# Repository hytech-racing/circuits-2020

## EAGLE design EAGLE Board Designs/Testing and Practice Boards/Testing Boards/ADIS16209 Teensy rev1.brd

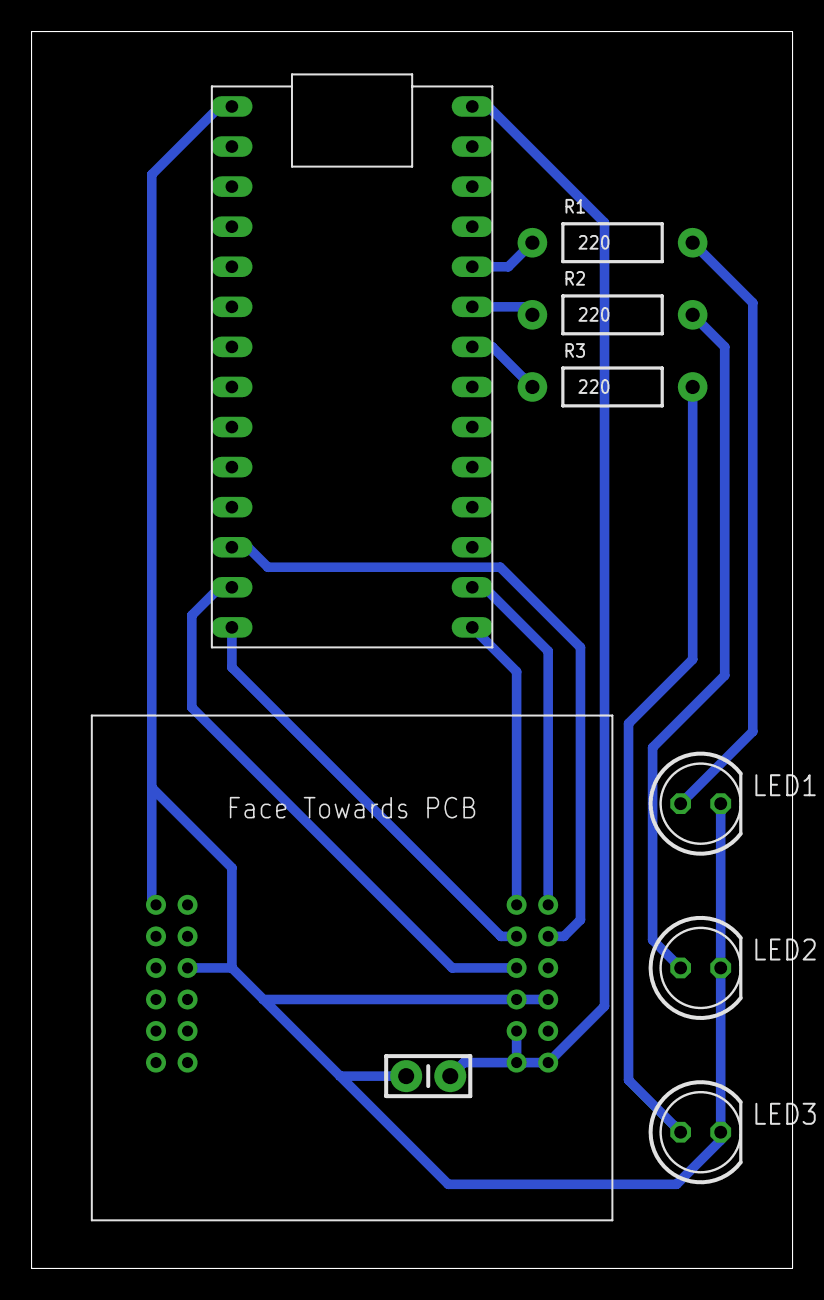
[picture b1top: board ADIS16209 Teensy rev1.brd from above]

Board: 2 copper layers, 48.2 x 78.4 mm, 9 parts (0 on the bottom side), 13 nets.

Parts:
C1: 1uF; CAP-PTH-SMALL-KIT
LED1, LED2, LED3: LED-5MM
R1, R2, R3: 220; AXIAL-0.4
U$1: ADIS16209/PCB
U$2: TEENSY_3.2_SIMPLE

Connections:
+3V3: C1.2, U$1.P$10, U$1.P$11, U$1.P$12, U$2.VIN
CS: U$1.P$3, U$2.D10(TX2)
GND: C1.1, LED1.K, LED2.K, LED3.K, U$1.P$7, U$1.P$8, U$1.P$14, U$1.P$17, U$2.GND
MISO: U$1.P$4, U$2.D12
MOSI: U$1.P$6, U$2.D11
unnamed: LED1.A, R1.P$2
unnamed: U$1.P$1, U$2.A0
unnamed: R1.P$1, U$2.A8
unnamed: R2.P$1, U$2.A7
unnamed: R3.P$1, U$2.A6
unnamed: LED2.A, R2.P$2
unnamed: LED3.A, R3.P$2
SCK: U$1.P$2, U$2.D13

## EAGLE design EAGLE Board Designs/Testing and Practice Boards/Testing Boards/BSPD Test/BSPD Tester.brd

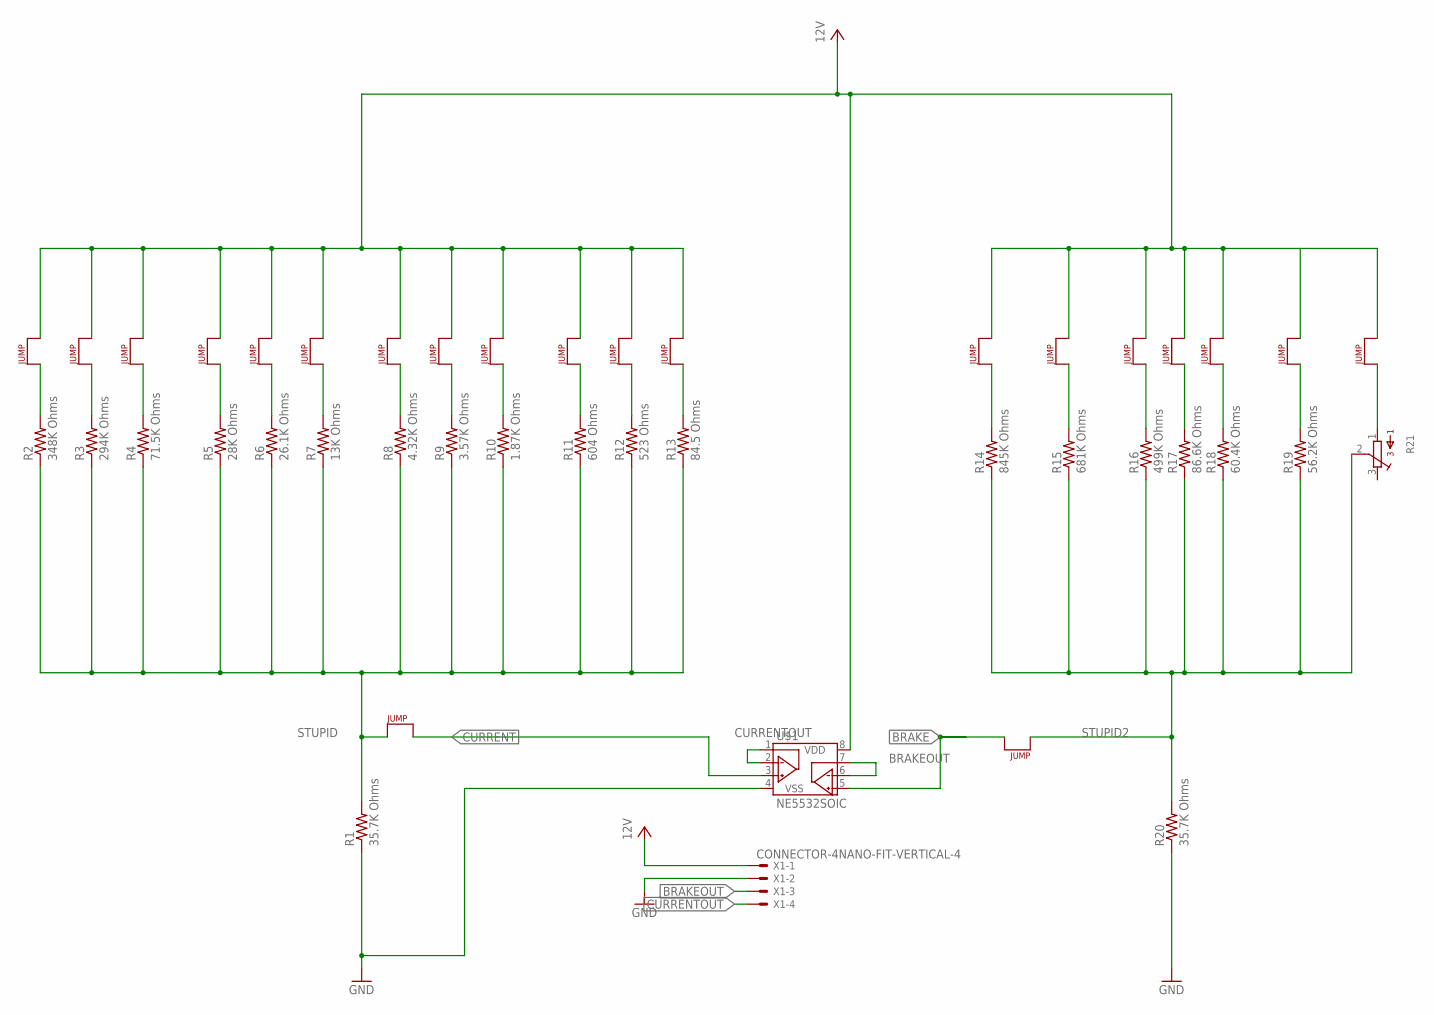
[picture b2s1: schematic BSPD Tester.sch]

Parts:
J1, J2, J3, J4, J5, J6, J7, J8, J9, J10, J11, J12, J13, J14, J15, J16, J17, J18, J19, J20, J21: JUMPER.1; 1X02
R1, R20: 35.7K Ohms; 1206
R2: 348K Ohms; 1206
R3: 294K Ohms; 1206
R4: 71.5K Ohms; 1206
R5: 28K Ohms; 1206
R6: 26.1K Ohms; 1206
R7: 13K Ohms; 1206
R8: 4.32K Ohms; 1206
R9: 3.57K Ohms; 1206
R10: 1.87K Ohms; 1206
R11: 604 Ohms; 1206
R12: 523 Ohms; 1206
R13: 84.5 Ohms; 1206
R14: 845K Ohms; 1206
R15: 681K Ohms; 1206
R16: 499K Ohms; 1206
R17: 86.6K Ohms; 1206
R18: 60.4K Ohms; 1206
R19: 56.2K Ohms; 1206
R21: TRIMPOT_3296C; TRIMPOT_3296
U$1: NE5532SOIC; SOIC-08
X1: CONNECTOR-4NANO-FIT-VERTICAL-4; NANO-FIT_VERTICAL-4

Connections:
BRAKE: J21.2, U$1.5 (VINB+)
BRAKEOUT: U$1.6 (VINB-), U$1.7 (VOUTB), X1.P$3
CURRENT: J19.2, U$1.3 (VINA+)
CURRENTOUT: U$1.1 (VOUTA), U$1.2 (VINA-), X1.P$4
GND: R1.1, R20.1, U$1.4 (VSS), X1.P$2
unnamed: J1.1, R2.2
unnamed: J13.1, R14.2
unnamed: J2.1, R3.2
unnamed: J3.1, R4.2
unnamed: J4.1, R5.2
unnamed: J5.1, R6.2
unnamed: J6.1, R7.2
unnamed: J7.1, R8.2
unnamed: J8.1, R9.2
unnamed: J9.1, R10.2
unnamed: J10.1, R11.2
unnamed: J11.1, R12.2
unnamed: J12.1, R13.2
unnamed: J14.1, R15.2
unnamed: J15.1, R16.2
unnamed: J16.1, R17.2
unnamed: J17.1, R18.2
unnamed: J18.1, R19.2
unnamed: J20.1, R21.1
STUPID: J19.1, R1.2, R2.1, R3.1, R4.1, R5.1, R6.1, R7.1, R8.1, R9.1, R10.1, R11.1, R12.1, R13.1
STUPID2: J21.1, R14.1, R15.1, R16.1, R17.1, R18.1, R19.1, R20.2, R21.2
VCC: J1.2, J2.2, J3.2, J4.2, J5.2, J6.2, J7.2, J8.2, J9.2, J10.2, J11.2, J12.2, J13.2, J14.2, J15.2, J16.2, J17.2, J18.2, J20.2, U$1.8 (VDD), X1.P$1

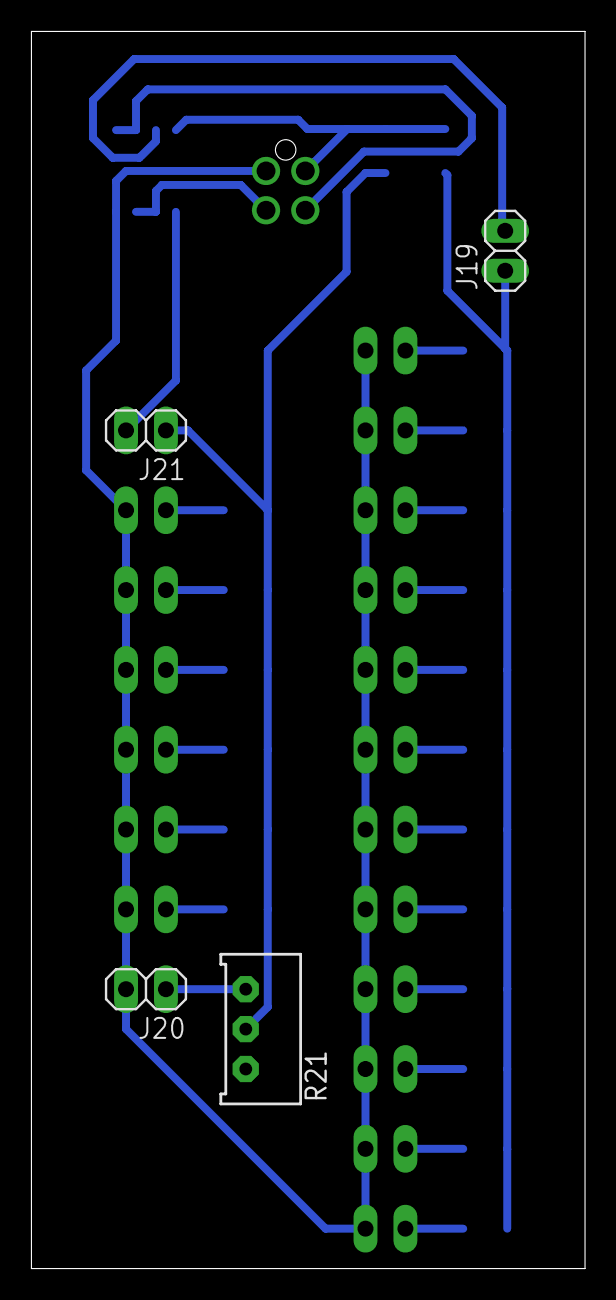
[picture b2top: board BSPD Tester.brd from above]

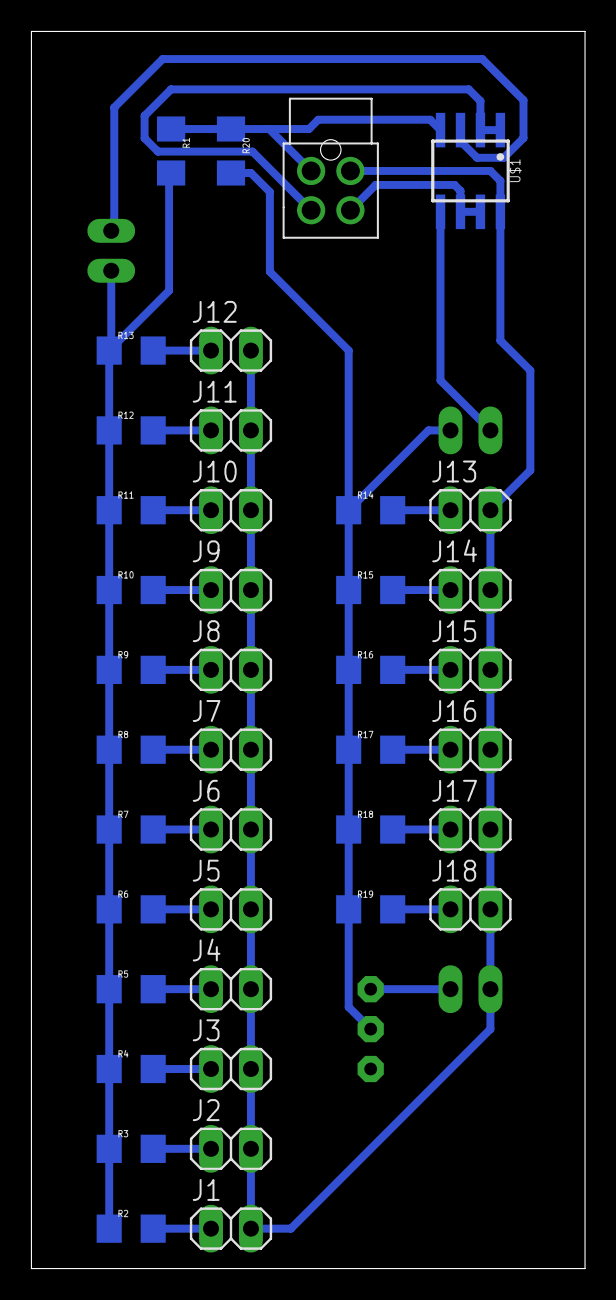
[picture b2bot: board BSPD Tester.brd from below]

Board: 2 copper layers, 35.2 x 78.7 mm, 44 parts (40 on the bottom side), 27 nets.

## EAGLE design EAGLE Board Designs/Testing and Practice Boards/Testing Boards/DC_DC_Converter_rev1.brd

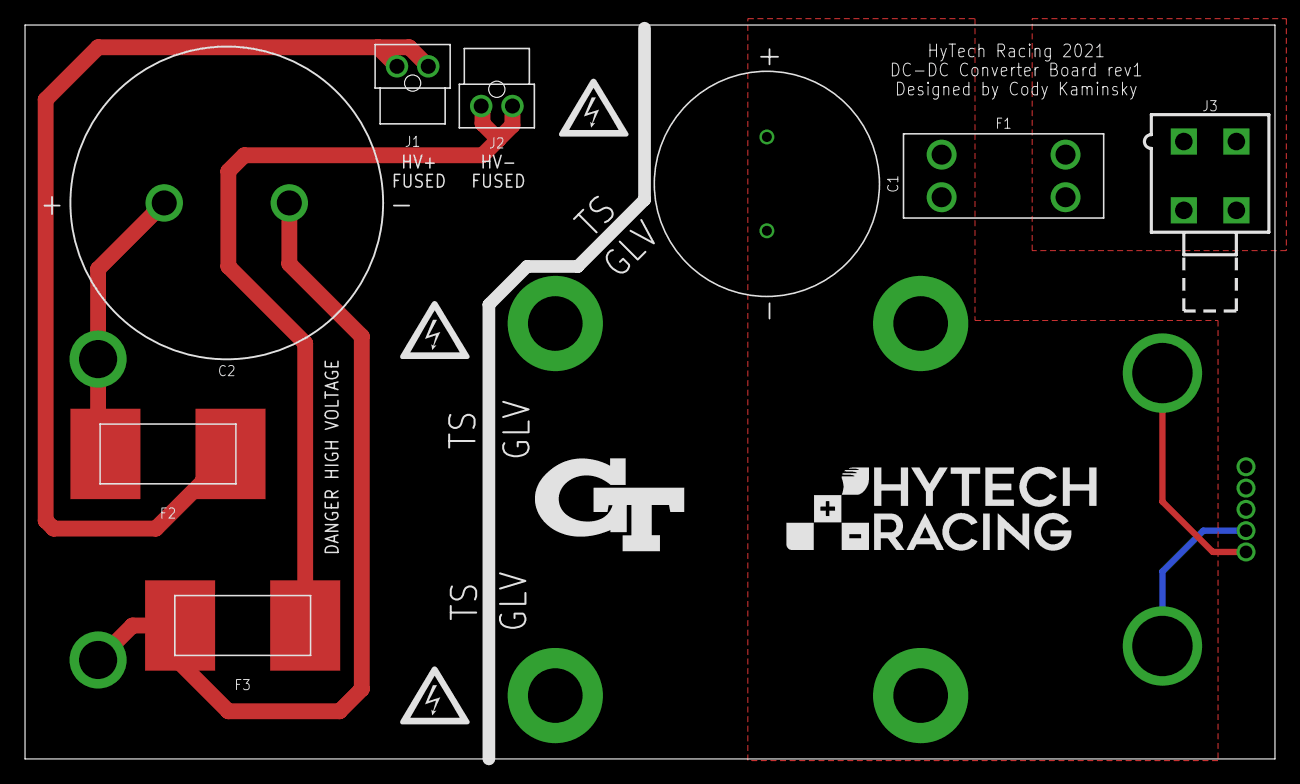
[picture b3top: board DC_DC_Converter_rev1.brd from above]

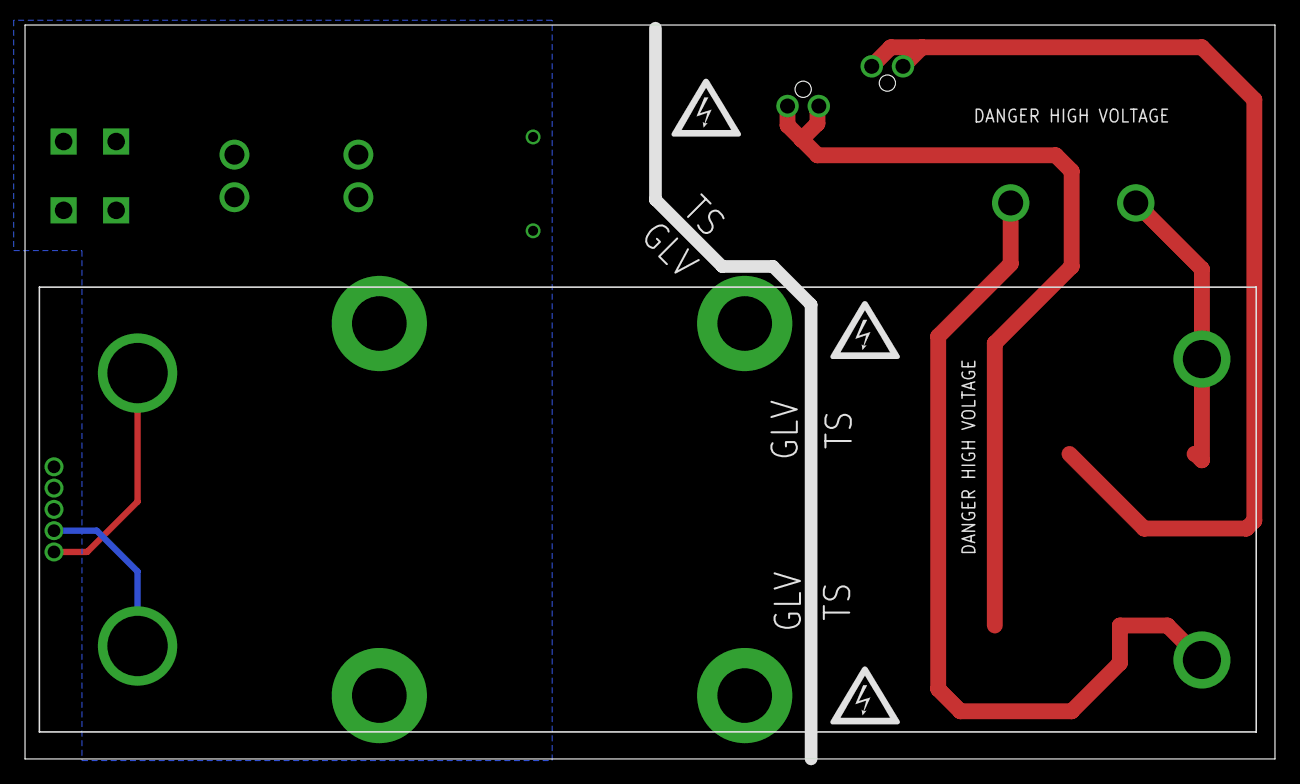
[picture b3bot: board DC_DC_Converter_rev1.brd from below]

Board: 2 copper layers, 99.9 x 58.7 mm, 17 parts (4 on the bottom side), 7 nets.

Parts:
C1: 4.7 mF; EKYC*MM
C2: LGG2G181MELA25; L*A
F1: MINI-BLADE_FUSE_HOLDER
F2, F3: 885_FUSE; 0885
J1, J2: MOLEX_NANOFIT_PTH_02
J3: MOLEX_MINIFIT_PTH_04
U1: DCM3714BD2K13E0C09; 3714DCM_VIA
U$1, U$2, U$3, U$8, U$9, U$10: HV_0.50"
U$6: LOGO_HYTECH_1.0"
U$7: LOGO_GT_0.50"

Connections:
12V_UNFUSED: C1.+, F1.L1, F1.L2, U1.3, U1.9
+12V: F1.R1, F1.R2, J3.1, J3.2
GND: C1.-, J3.3, J3.4, U1.4, U1.8
HV+: F2.1, J1.1, J1.2
HV-: F3.1, J2.1, J2.2
IN+: C2.+, F2.2, U1.1
IN-: C2.-, F3.2, U1.2

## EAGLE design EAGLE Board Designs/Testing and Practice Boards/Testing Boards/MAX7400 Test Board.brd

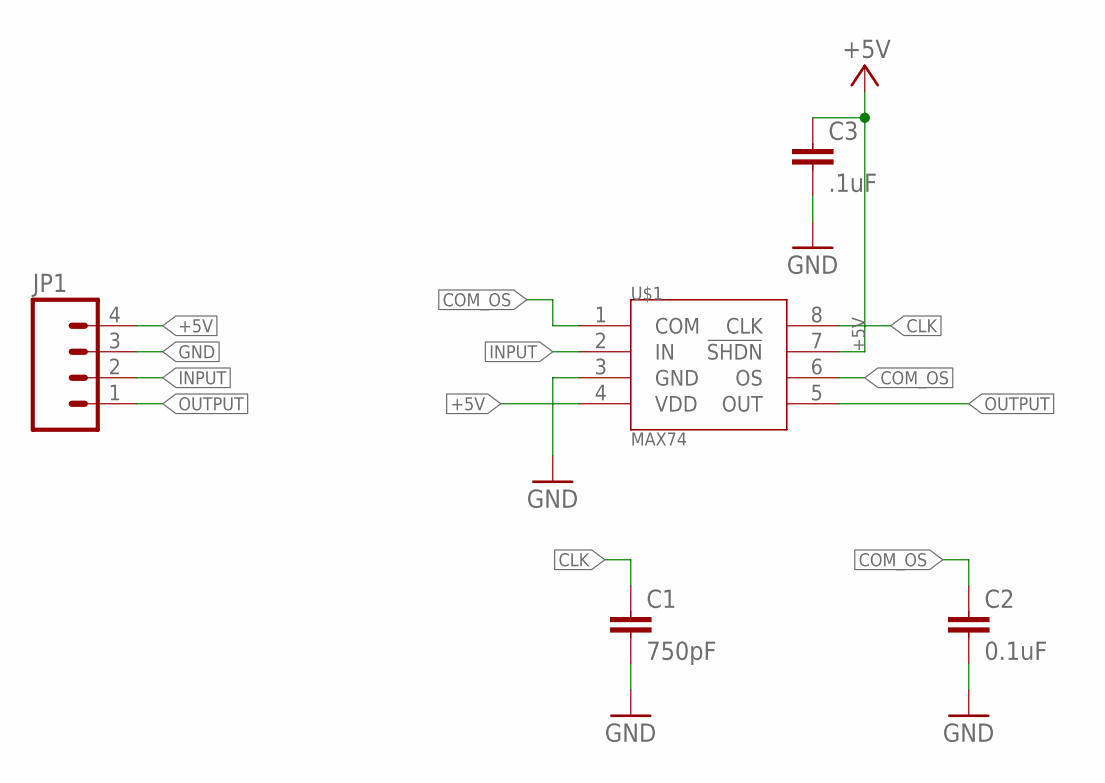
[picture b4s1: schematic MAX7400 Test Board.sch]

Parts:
C1: 750pF; 0603-CAP
C2: 0.1uF; 0603-CAP
C3: .1uF; 0603-CAP
JP1: M04; 1X04
U$1: MAX74; SOP8

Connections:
+5V: C3.1, JP1.4, U$1.4 (VDD), U$1.7 (!SHDN)
CLK: C1.1, U$1.8 (CLK)
COM_OS: C2.1, U$1.1 (COM), U$1.6 (OS)
GND: C1.2, C2.2, C3.2, JP1.3, U$1.3 (GND)
INPUT: JP1.2, U$1.2 (IN)
OUTPUT: JP1.1, U$1.5 (OUT)

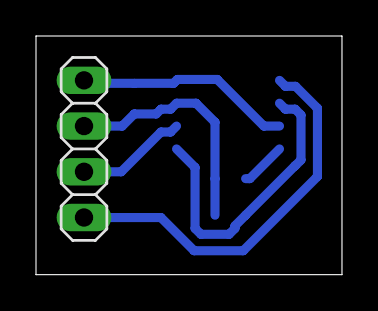
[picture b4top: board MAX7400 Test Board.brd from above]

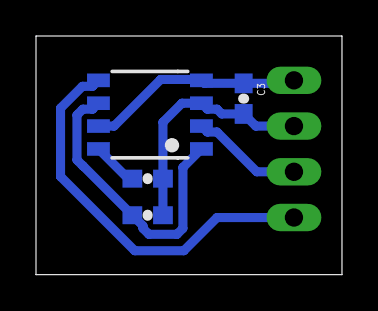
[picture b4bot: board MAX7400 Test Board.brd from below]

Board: 2 copper layers, 17.0 x 13.3 mm, 5 parts (4 on the bottom side), 6 nets.

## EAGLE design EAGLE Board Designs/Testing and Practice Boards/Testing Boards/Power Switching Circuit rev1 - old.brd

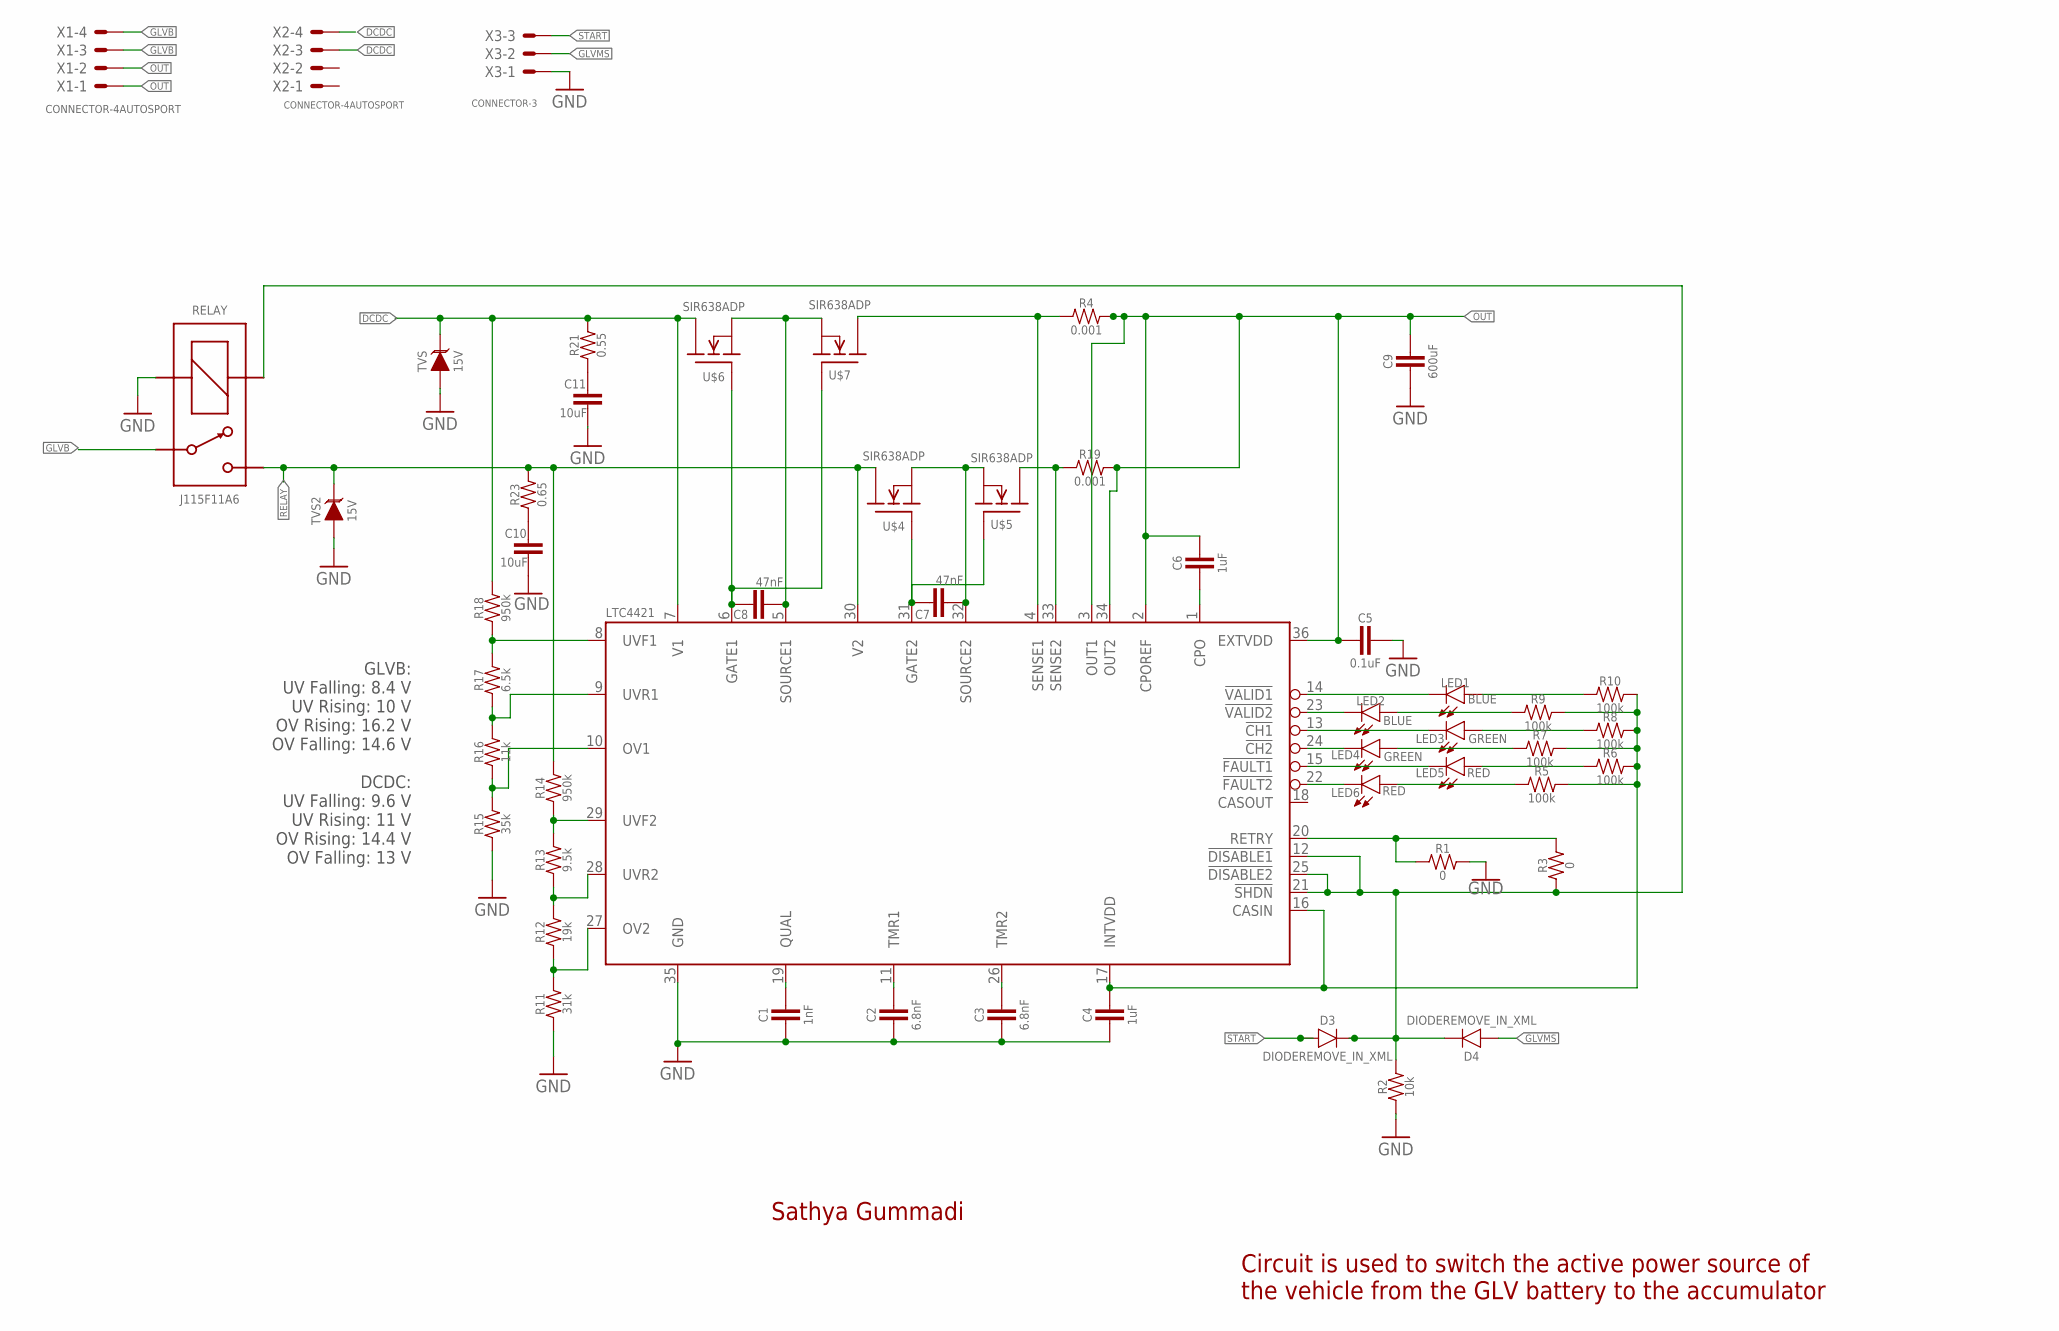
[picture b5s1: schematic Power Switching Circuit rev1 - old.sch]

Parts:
C1: 1nF; 0603-CAP
C2, C3: 6.8nF; 0603-CAP
C4, C6: 1uF; 0603-CAP
C5: 0.1uF; 0603-CAP
C7, C8: 47nF; 0603-CAP
C9: 600uF; 0603-CAP
C10, C11: 10uF; 0603-CAP
D3, D4: DIODEREMOVE_IN_XML; 0805_D
LED1, LED2: BLUE; LED-603
LED3, LED4: GREEN; LED-603
LED5, LED6: RED; LED-603
LTC4421: LTC4421; SSOP-36
R1, R3: 0; 0603-RES
R2: 10k; 0603-RES
R4, R19: 0.001; 5930-SENSE_RES
R5, R6, R7, R8, R9, R10: 100k; 0603-RES
R11: 31k; 0603-RES
R12: 19k; 0603-RES
R13: 9.5k; 0603-RES
R14, R18: 950k; 0603-RES
R15: 35k; 0603-RES
R16: 11k; 0603-RES
R17: 6.5k; 0603-RES
R21: 0.55; 0805
R23: 0.65; 0805
RELAY: J115F11A6; J115F11A*6*
TVS, TVS2: TVS_15V; SOT-23
U$4, U$5, U$6, U$7: SIR638ADP; SO-8-POWERPAK
X1, X2: CONNECTOR-4AUTOSPORT; AUTOSPORT_12-04
X3: CONNECTOR-3; AUTOSPORT_04-35

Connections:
!CH1: LED3.C, LTC4421.13 (!CH1)
!CH2: LED4.C, LTC4421.24 (!CH2)
!FAULT1: LED5.C, LTC4421.15 (!FAULT1)
!FAULT2: LED6.C, LTC4421.22 (!FAULT2)
!SHDN: D3.C, D4.C, LTC4421.12 (!DISABLE1), LTC4421.21 (!SHDN), LTC4421.25 (!DISABLE2), R2.2, R3.1, RELAY.COIL1 (COIL+)
!VALID1: LED1.C, LTC4421.14 (!VALID1)
!VALID2: LED2.C, LTC4421.23 (!VALID2)
CASIN: C4.1, LTC4421.16 (CASIN), LTC4421.17 (INTVDD), R5.2, R6.2, R7.2, R8.2, R9.2, R10.2
CPO: C6.2, LTC4421.1 (CPO)
DCDC: LTC4421.7 (V1), R18.2, R21.2, TVS.3 (C), U$6.D@5 (D), U$6.D@6 (D), U$6.D@7 (D), U$6.D@8 (D), U$6.D@PAD (D), X2.3, X2.4
GATE1: C8.2, LTC4421.6 (GATE1), U$6.4 (G), U$7.4 (G)
GATE2: C7.2, LTC4421.31 (GATE2), U$4.4 (G), U$5.4 (G)
GLVB: RELAY.CONTACT1, X1.3, X1.4
GLVMS: D4.A, X3.B
GND: C1.2, C2.2, C3.2, C4.2, C5.1, C9.2, C10.2, C11.2, LTC4421.35 (GND), R1.2, R2.1, R11.1, R15.1, RELAY.COIL2 (COIL-), TVS.1 (A), TVS2.1 (A), X3.A
unnamed: C1.1, LTC4421.19 (QUAL)
unnamed: C2.1, LTC4421.11 (TMR1)
unnamed: C3.1, LTC4421.26 (TMR2)
unnamed: C10.1, R23.1
unnamed: LED6.A, R5.1
unnamed: LED5.A, R6.1
unnamed: LED4.A, R7.1
unnamed: LED3.A, R8.1
unnamed: LED2.A, R9.1
unnamed: LED1.A, R10.1
unnamed: C11.1, R21.1
OUT: C5.2, C6.1, C9.1, LTC4421.2 (CPOREF), LTC4421.3 (OUT1), LTC4421.34 (OUT2), LTC4421.36 (EXTVDD), R4.2, R19.2, X1.1, X1.2
OV1: LTC4421.10 (OV1), R15.2, R16.1
OV2: LTC4421.27 (OV2), R11.2, R12.1
RELAY: LTC4421.30 (V2), R14.2, R23.2, RELAY.CONTACT2 (S), TVS2.3 (C), U$4.D@5 (D), U$4.D@6 (D), U$4.D@7 (D), U$4.D@8 (D), U$4.D@PAD (D)
RETRY: LTC4421.20 (RETRY), R1.1, R3.2
SENSE: LTC4421.4 (SENSE1), R4.1, U$7.D@5 (D), U$7.D@6 (D), U$7.D@7 (D), U$7.D@8 (D), U$7.D@PAD (D)
SENSE2: LTC4421.33 (SENSE2), R19.1, U$5.D@5 (D), U$5.D@6 (D), U$5.D@7 (D), U$5.D@8 (D), U$5.D@PAD (D)
SOURCE1: C8.1, LTC4421.5 (SOURCE1), U$6.1 (S), U$6.2 (S), U$6.3 (S), U$7.1 (S), U$7.2 (S), U$7.3 (S)
SOURCE2: C7.1, LTC4421.32 (SOURCE2), U$4.1 (S), U$4.2 (S), U$4.3 (S), U$5.1 (S), U$5.2 (S), U$5.3 (S)
START: D3.A, X3.C
UVF1: LTC4421.8 (UVF1), R17.2, R18.1
UVF2: LTC4421.29 (UVF2), R13.2, R14.1
UVR1: LTC4421.9 (UVR1), R16.2, R17.1
UVR2: LTC4421.28 (UVR2), R12.2, R13.1

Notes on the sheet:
Sathya Gummadi
Circuit is used to switch the active power source of the vehicle from the GLV battery to the accumulator
GLVB: UV Falling: 8.4 V UV Rising: 10 V OV Rising: 16.2 V OV Falling: 14.6 V DCDC: UV Falling: 9.6 V UV Rising: 11 V OV Rising: 14.4 V OV Falling: 13 V

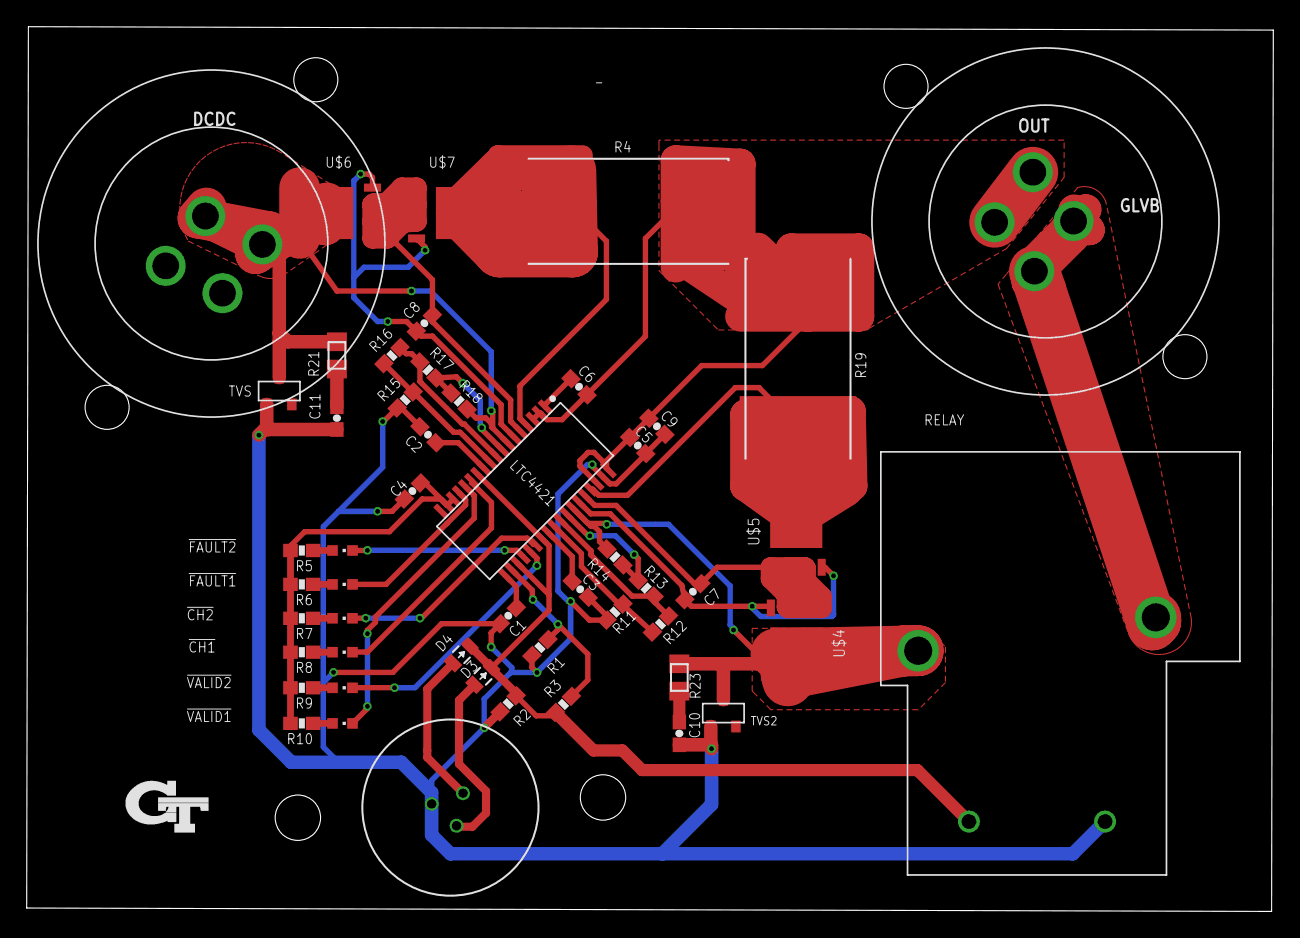
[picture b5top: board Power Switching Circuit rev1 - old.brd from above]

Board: 2 copper layers, 93.4 x 66.3 mm, 51 parts (0 on the bottom side), 40 nets.

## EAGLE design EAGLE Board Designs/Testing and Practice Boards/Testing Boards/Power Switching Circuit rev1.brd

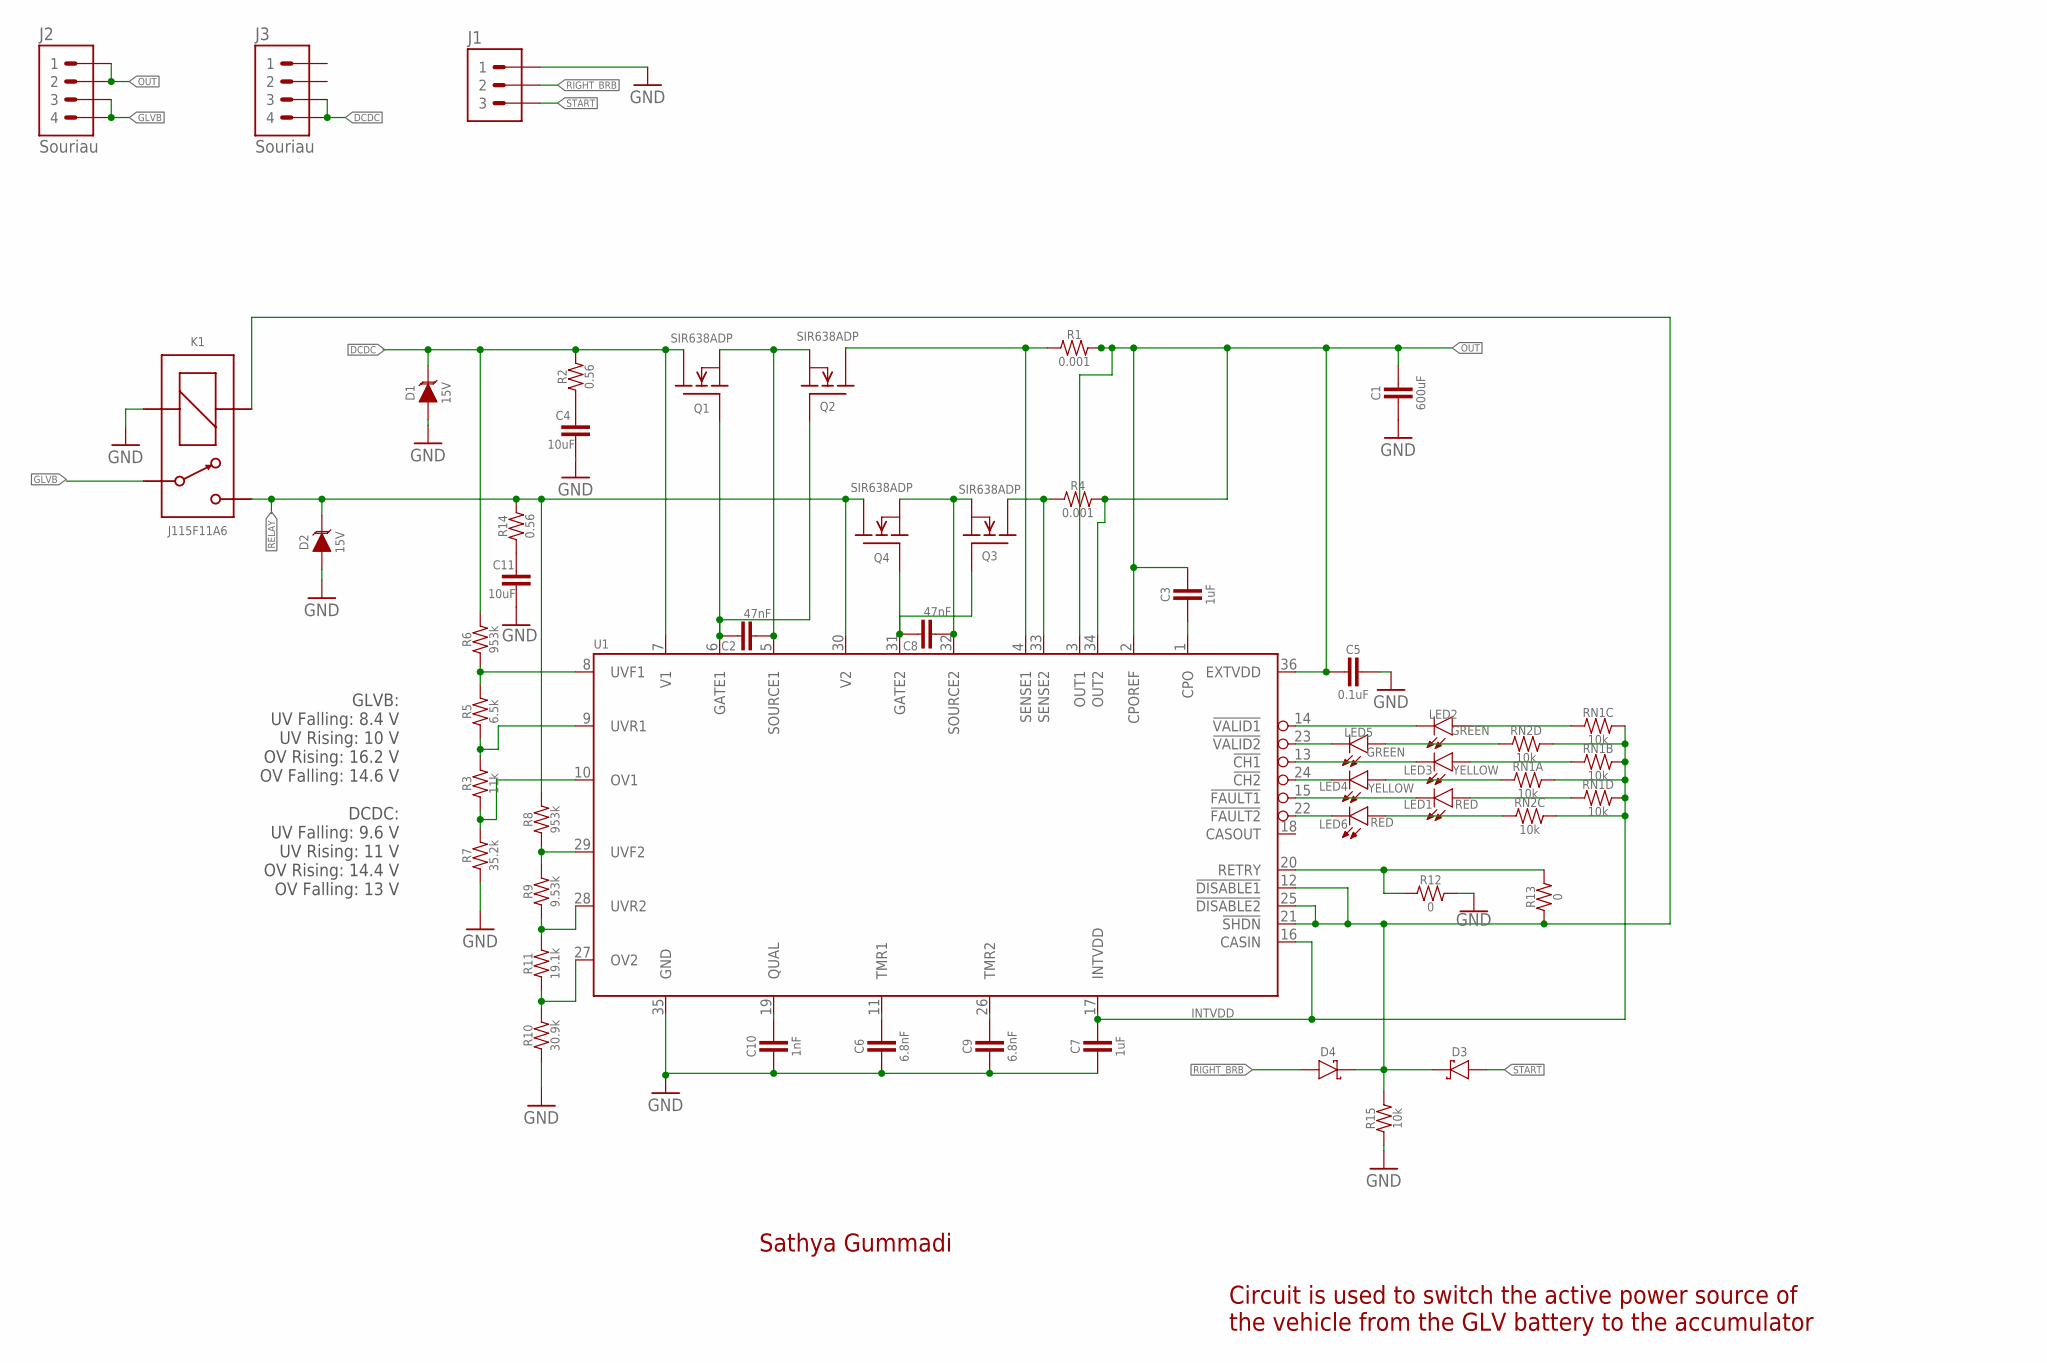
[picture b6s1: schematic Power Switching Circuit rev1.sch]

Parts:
C1: 600uF; 0603-CAP
C2, C8: 47nF; 0603-CAP
C3, C7: 1uF; 0603-CAP
C4, C11: 10uF; 0603-CAP
C5: 0.1uF; 0603-CAP
C6, C9: 6.8nF; 0603-CAP
C10: 1nF; 0603-CAP
D1, D2: TVS_15V; SOT-23
D3, D4: SCHOTTKY; CLP1608-2L
J1: CONNECTOR-3_; SOURIAU_04-35
J2, J3: CONNECTOR-4_SOURIAU_; SOURIAU_12-04
K1: J115F11A6; J115F11A*6*
LED1, LED6: RED; LED-603
LED2, LED5: GREEN; LED-603
LED3, LED4: YELLOW; LED-603
Q1, Q2, Q3, Q4: SIR638ADP; POWERPAK_SO-8
R1, R4: 0.001; 5930-SENSE_RES
R2, R14: 0.56; 0805
R3: 11k; 0603-RES
R5: 6.5k; 0603-RES
R6, R8: 953k; 0603-RES
R7: 35.2k; 0603-RES
R9: 9.53k; 0603-RES
R10: 30.9k; 0603-RES
R11: 19.1k; 0603-RES
R12, R13: 0; 0603-RES
R15: 10k; 0603-RES
RN1, RN2: RESISTOR_NETWORK_4_10K; YC/TC164
U1: LTC4421; SSOP-36

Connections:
!CH1: LED3.C, U1.13 (!CH1)
!CH2: LED4.C, U1.24 (!CH2)
!FAULT1: LED1.C, U1.15 (!FAULT1)
!FAULT2: LED6.C, U1.22 (!FAULT2)
!SHDN!: D3.2 (C), D4.2 (C), K1.COIL1 (COIL+), R13.1, R15.2, U1.12 (!DISABLE1), U1.21 (!SHDN), U1.25 (!DISABLE2)
!VALID1: LED2.C, U1.14 (!VALID1)
!VALID2: LED5.C, U1.23 (!VALID2)
CPO: C3.2, U1.1 (CPO)
DCDC: D1.3 (C), J3.3, J3.4, Q1.D@5 (D), Q1.D@6 (D), Q1.D@7 (D), Q1.D@8 (D), Q1.D@PAD (D), R2.2, R6.2, U1.7 (V1)
GATE1: C2.2, Q1.4 (G), Q2.4 (G), U1.6 (GATE1)
GATE2: C8.2, Q3.4 (G), Q4.4 (G), U1.31 (GATE2)
GLVB: J2.3, J2.4, K1.CONTACT1
GND: C1.2, C4.2, C5.1, C6.2, C7.2, C9.2, C10.2, C11.2, D1.1 (A), D2.1 (A), J1.A (1), K1.COIL2 (COIL-), R7.1, R10.1, R12.2, R15.1, U1.35 (GND)
INTVDD: C7.1, RN1.5 (2), RN1.6 (2), RN1.7 (2), RN1.8 (2), RN2.5 (2), RN2.6 (2), U1.16 (CASIN), U1.17 (INTVDD)
unnamed: C10.1, U1.19 (QUAL)
unnamed: C6.1, U1.11 (TMR1)
unnamed: C9.1, U1.26 (TMR2)
unnamed: C11.1, R14.1
unnamed: LED6.A, RN2.3 (1)
unnamed: LED1.A, RN1.4 (1)
unnamed: LED4.A, RN1.1
unnamed: LED3.A, RN1.2 (1)
unnamed: LED5.A, RN2.4 (1)
unnamed: LED2.A, RN1.3 (1)
unnamed: C4.1, R2.1
OUT: C1.1, C3.1, C5.2, J2.1, J2.2, R1.2, R4.2, U1.2 (CPOREF), U1.3 (OUT1), U1.34 (OUT2), U1.36 (EXTVDD)
OV1: R3.1, R7.2, U1.10 (OV1)
OV2: R10.2, R11.1, U1.27 (OV2)
RELAY: D2.3 (C), K1.CONTACT2 (S), Q4.D@5 (D), Q4.D@6 (D), Q4.D@7 (D), Q4.D@8 (D), Q4.D@PAD (D), R8.2, R14.2, U1.30 (V2)
RETRY: R12.1, R13.2, U1.20 (RETRY)
RIGHT_BRB: D4.1 (A), J1.B (2)
SENSE: Q2.D@5 (D), Q2.D@6 (D), Q2.D@7 (D), Q2.D@8 (D), Q2.D@PAD (D), R1.1, U1.4 (SENSE1)
SENSE2: Q3.D@5 (D), Q3.D@6 (D), Q3.D@7 (D), Q3.D@8 (D), Q3.D@PAD (D), R4.1, U1.33 (SENSE2)
SOURCE1: C2.1, Q1.1 (S), Q1.2 (S), Q1.3 (S), Q2.1 (S), Q2.2 (S), Q2.3 (S), U1.5 (SOURCE1)
SOURCE2: C8.1, Q3.1 (S), Q3.2 (S), Q3.3 (S), Q4.1 (S), Q4.2 (S), Q4.3 (S), U1.32 (SOURCE2)
START: D3.1 (A), J1.C (3)
UVF1: R5.2, R6.1, U1.8 (UVF1)
UVF2: R8.1, R9.2, U1.29 (UVF2)
UVR1: R3.2, R5.1, U1.9 (UVR1)
UVR2: R9.1, R11.2, U1.28 (UVR2)

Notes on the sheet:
Sathya Gummadi
Circuit is used to switch the active power source of the vehicle from the GLV battery to the accumulator
GLVB: UV Falling: 8.4 V UV Rising: 10 V OV Rising: 16.2 V OV Falling: 14.6 V DCDC: UV Falling: 9.6 V UV Rising: 11 V OV Rising: 14.4 V OV Falling: 13 V

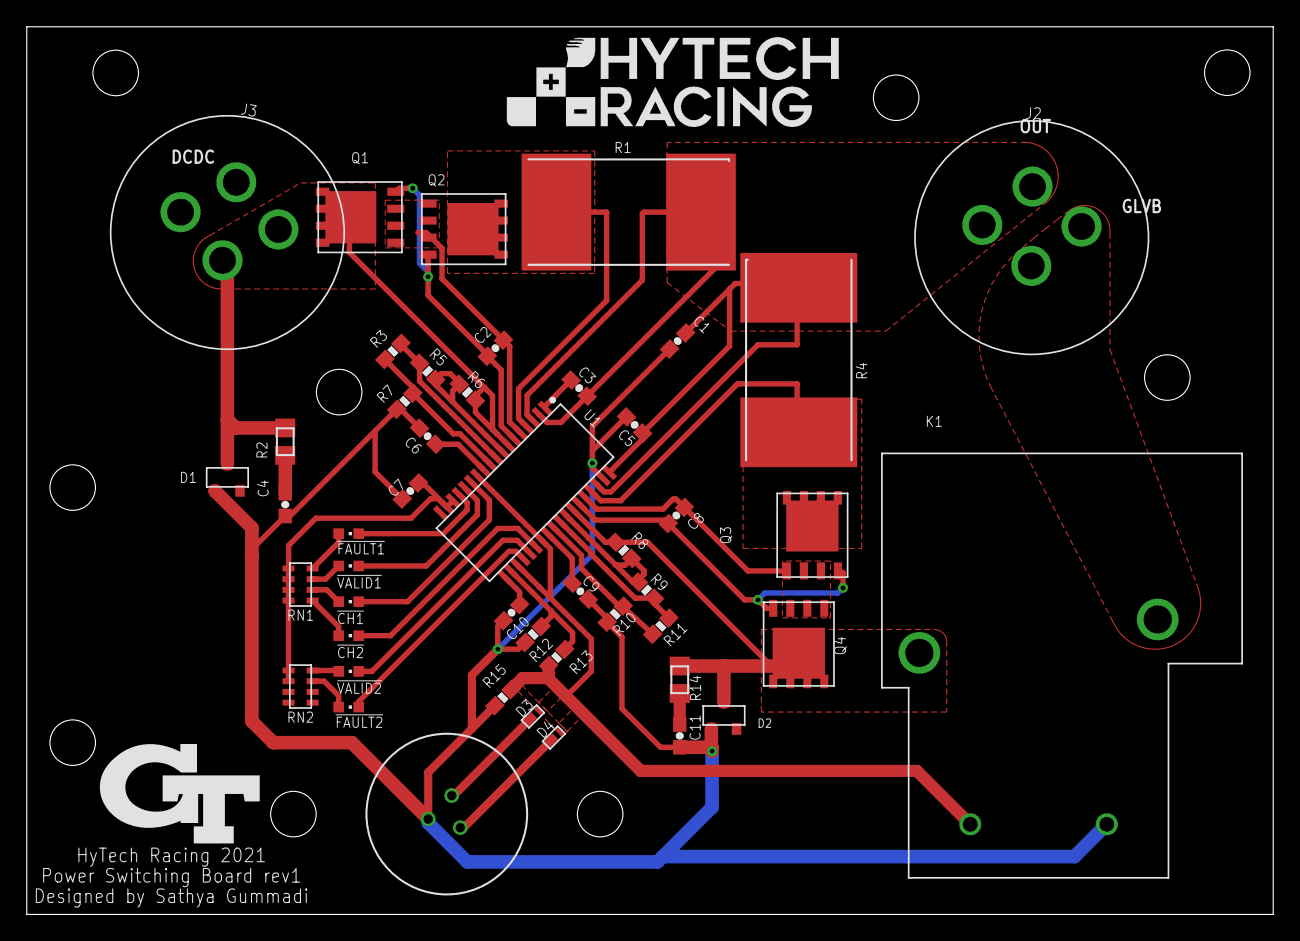
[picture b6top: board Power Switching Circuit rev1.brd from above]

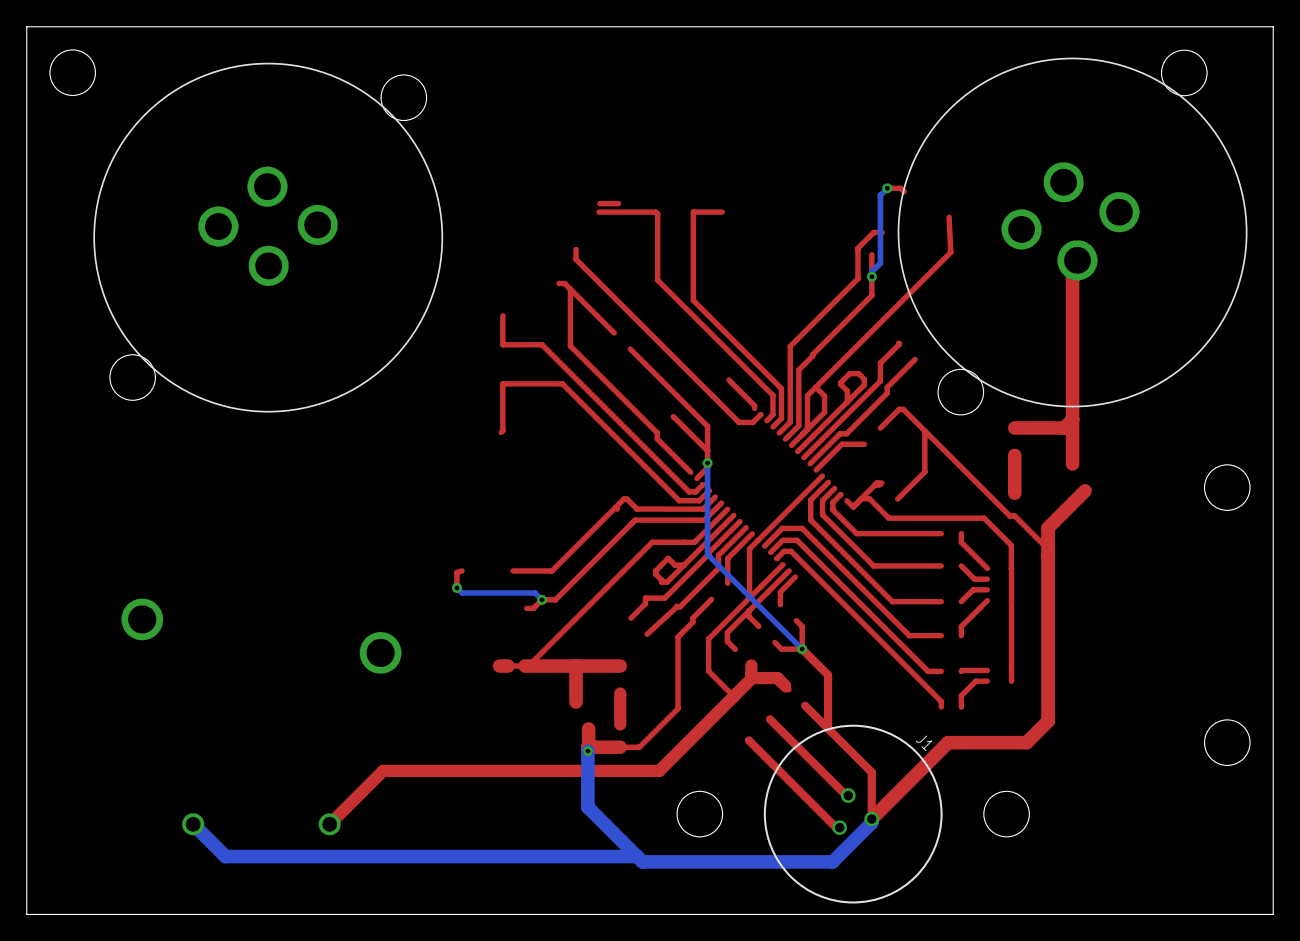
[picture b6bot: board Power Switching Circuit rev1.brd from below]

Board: 2 copper layers, 93.1 x 66.3 mm, 52 parts (3 on the bottom side), 40 nets.

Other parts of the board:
U$1, U$3, U$4: MOUNTING_M3
U$5: LOGO_GT_0.50"
U$6: LOGO_HYTECH_1.0"
